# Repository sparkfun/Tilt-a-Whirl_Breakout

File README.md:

Tilt-a-Whirl Breakout Board
=====================

Note: The RPI-1031 IC is EOL and discontinuted by the manufacturer. Therefore, the tilt-a-whirl breakout has been retired.

[  
*RPI-1031 Tilt-a-Whirl Breakout(SEN-12011)*](https://www.sparkfun.com/products/12011)

The RPI-1031 tilt sensor is capable of sensing a change in orientation in four different directions: forward, back, left, or right.

Repository Contents
-------------------
* **/Firmware** - Example Arduino sketch for interfacing with the breakout board. 
* **/Hardware** - All Eagle design files (.brd, .sch)
* **/Production** - Test bed files and production panel files

Product Versions
----------------
* [SEN-12011 (RETIRED)](https://www.sparkfun.com/products/12011)- V12 of the Tilt-a-Whirl
* [SEN-10621 (RETIRED)](https://www.sparkfun.com/products/10621)- V11 of the Tilt-a-Whirl

License Information
-------------------
The hardware is released under [Creative Commons Share-alike 3.0](http://creativecommons.org/licenses/by-sa/3.0/).  
All other code is open source so please feel free to do anything you want with it; 
you buy me a beer if you use this and we meet someday ([Beerware license](http://en.wikipedia.org/wiki/Beerware)).

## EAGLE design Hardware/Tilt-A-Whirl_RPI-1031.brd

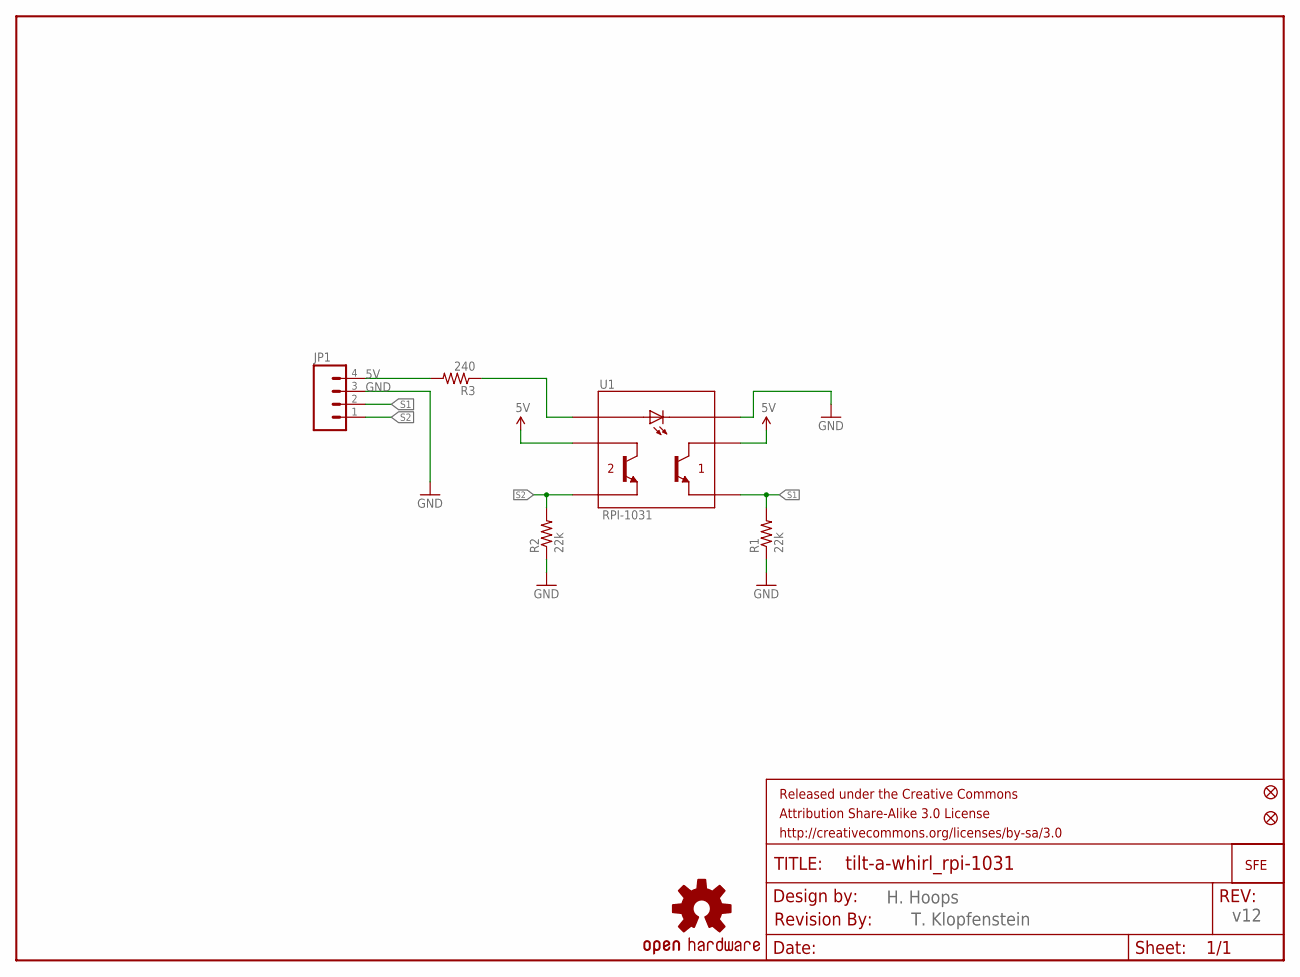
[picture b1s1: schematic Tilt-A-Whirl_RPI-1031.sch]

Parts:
FRAME1: FRAME-LETTER; CREATIVE_COMMONS
JP1: M04PTH; 1X04
JP2, JP3: FIDUCIAL1X2.5; FIDUCIAL-1X2.5
JP4: LOGO-SFESK; SFE-LOGO-FLAME
R1, R2: 22k; 0603-RES
R3: 240; 0603-RES
U1: RPI-1031
U$1: OSHW-LOGOS; OSHW-LOGO-S
U$2: REVISION

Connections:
5V: JP1.4, R3.2, U1.2 (C1), U1.5 (C2)
AN: R3.1, U1.6 (ANODE)
GND: JP1.3, R1.1, R2.1, U1.3 (CATHODE)
S1: JP1.2, R1.2, U1.1 (E1)
S2: JP1.1, R2.2, U1.4 (E2)

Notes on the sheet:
H. Hoops
T. Klopfenstein
v12

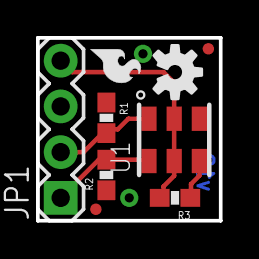
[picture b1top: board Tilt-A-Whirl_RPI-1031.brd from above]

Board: 2 copper layers, 10.2 x 10.2 mm, 11 parts (0 on the bottom side), 5 nets.

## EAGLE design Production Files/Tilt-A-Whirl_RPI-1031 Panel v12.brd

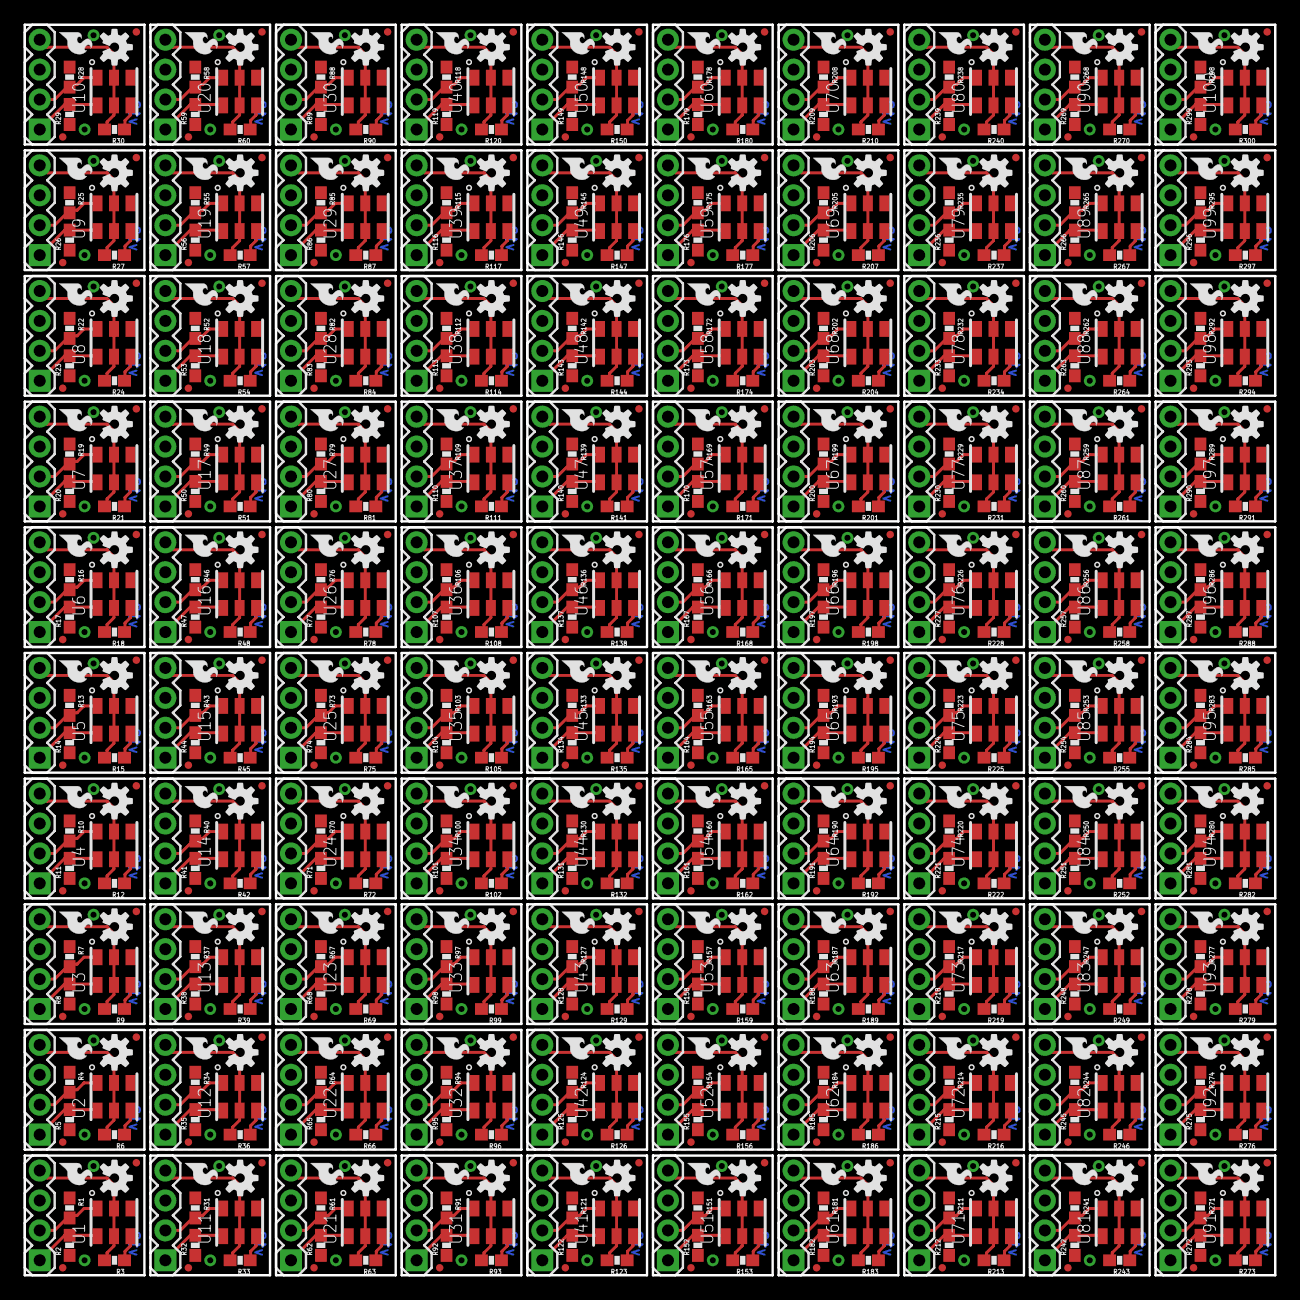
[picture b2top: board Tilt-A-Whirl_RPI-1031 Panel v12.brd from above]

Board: 2 copper layers, 106.2 x 106.2 mm, 900 parts (0 on the bottom side), 500 nets.

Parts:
JP1, JP6, JP10, JP14, JP18, JP22, JP26, JP30, JP34, JP38, JP42, JP46, JP50, JP54, JP58, JP62, JP66, JP70, JP74, JP78, JP82, JP86, JP90, JP94, JP98, JP102, JP106, JP110, JP114, JP118, JP122, JP126, JP130, JP134, JP138, JP142, JP146, JP150, JP154, JP158, JP162, JP166, JP170, JP174, JP178, JP182, JP186, JP190, JP194, JP198, JP202, JP206, JP210, JP214, JP218, JP222, JP226, JP230, JP234, JP238, JP242, JP246, JP250, JP254, JP258, JP262, JP266, JP270, JP274, JP278, JP282, JP286, JP290, JP294, JP298, JP302, JP306, JP310, JP314, JP318, JP322, JP326, JP330, JP334, JP338, JP342, JP346, JP350, JP354, JP358, JP362, JP366, JP370, JP374, JP378, JP382, JP386, JP390, JP394, JP398: 1X04
JP2, JP3, JP7, JP8, JP11, JP12, JP15, JP16, JP19, JP20, JP23, JP24, JP27, JP28, JP31, JP32, JP35, JP36, JP39, JP40, JP43, JP44, JP47, JP48, JP51, JP52, JP55, JP56, JP59, JP60, JP63, JP64, JP67, JP68, JP71, JP72, JP75, JP76, JP79, JP80, JP83, JP84, JP87, JP88, JP91, JP92, JP95, JP96, JP99, JP100, JP103, JP104, JP107, JP108, JP111, JP112, JP115, JP116, JP119, JP120, JP123, JP124, JP127, JP128, JP131, JP132, JP135, JP136, JP139, JP140, JP143, JP144, JP147, JP148, JP151, JP152, JP155, JP156, JP159, JP160, JP163, JP164, JP167, JP168, JP171, JP172, JP175, JP176, JP179, JP180, JP183, JP184, JP187, JP188, JP191, JP192, JP195, JP196, JP199, JP200, JP203, JP204, JP207, JP208, JP211, JP212, JP215, JP216, JP219, JP220, JP223, JP224, JP227, JP228, JP231, JP232, JP235, JP236, JP239, JP240, JP243, JP244, JP247, JP248, JP251, JP252, JP255, JP256, JP259, JP260, JP263, JP264, JP267, JP268, JP271, JP272, JP275, JP276, JP279, JP280, JP283, JP284, JP287, JP288, JP291, JP292, JP295, JP296, JP299, JP300, JP303, JP304, JP307, JP308, JP311, JP312, JP315, JP316, JP319, JP320, JP323, JP324, JP327, JP328, JP331, JP332, JP335, JP336, JP339, JP340, JP343, JP344, JP347, JP348, JP351, JP352, JP355, JP356, JP359, JP360, JP363, JP364, JP367, JP368, JP371, JP372, JP375, JP376, JP379, JP380, JP383, JP384, JP387, JP388, JP391, JP392, JP395, JP396, JP399, JP400: FIDUCIAL1X2.5; FIDUCIAL-1X2.5
JP4, JP5, JP9, JP13, JP17, JP21, JP25, JP29, JP33, JP37, JP41, JP45, JP49, JP53, JP57, JP61, JP65, JP69, JP73, JP77, JP81, JP85, JP89, JP93, JP97, JP101, JP105, JP109, JP113, JP117, JP121, JP125, JP129, JP133, JP137, JP141, JP145, JP149, JP153, JP157, JP161, JP165, JP169, JP173, JP177, JP181, JP185, JP189, JP193, JP197, JP201, JP205, JP209, JP213, JP217, JP221, JP225, JP229, JP233, JP237, JP241, JP245, JP249, JP253, JP257, JP261, JP265, JP269, JP273, JP277, JP281, JP285, JP289, JP293, JP297, JP301, JP305, JP309, JP313, JP317, JP321, JP325, JP329, JP333, JP337, JP341, JP345, JP349, JP353, JP357, JP361, JP365, JP369, JP373, JP377, JP381, JP385, JP389, JP393, JP397: LOGO-SFESK; SFE-LOGO-FLAME
R1, R2, R4, R5, R7, R8, R10, R11, R13, R14, R16, R17, R19, R20, R22, R23, R25, R26, R28, R29, R31, R32, R34, R35, R37, R38, R40, R41, R43, R44, R46, R47, R49, R50, R52, R53, R55, R56, R58, R59, R61, R62, R64, R65, R67, R68, R70, R71, R73, R74, R76, R77, R79, R80, R82, R83, R85, R86, R88, R89, R91, R92, R94, R95, R97, R98, R100, R101, R103, R104, R106, R107, R109, R110, R112, R113, R115, R116, R118, R119, R121, R122, R124, R125, R127, R128, R130, R131, R133, R134, R136, R137, R139, R140, R142, R143, R145, R146, R148, R149, R151, R152, R154, R155, R157, R158, R160, R161, R163, R164, R166, R167, R169, R170, R172, R173, R175, R176, R178, R179, R181, R182, R184, R185, R187, R188, R190, R191, R193, R194, R196, R197, R199, R200, R202, R203, R205, R206, R208, R209, R211, R212, R214, R215, R217, R218, R220, R221, R223, R224, R226, R227, R229, R230, R232, R233, R235, R236, R238, R239, R241, R242, R244, R245, R247, R248, R250, R251, R253, R254, R256, R257, R259, R260, R262, R263, R265, R266, R268, R269, R271, R272, R274, R275, R277, R278, R280, R281, R283, R284, R286, R287, R289, R290, R292, R293, R295, R296, R298, R299: 22k; 0603-RES
R3, R6, R9, R12, R15, R18, R21, R24, R27, R30, R33, R36, R39, R42, R45, R48, R51, R54, R57, R60, R63, R66, R69, R72, R75, R78, R81, R84, R87, R90, R93, R96, R99, R102, R105, R108, R111, R114, R117, R120, R123, R126, R129, R132, R135, R138, R141, R144, R147, R150, R153, R156, R159, R162, R165, R168, R171, R174, R177, R180, R183, R186, R189, R192, R195, R198, R201, R204, R207, R210, R213, R216, R219, R222, R225, R228, R231, R234, R237, R240, R243, R246, R249, R252, R255, R258, R261, R264, R267, R270, R273, R276, R279, R282, R285, R288, R291, R294, R297, R300: 240; 0603-RES
U1, U2, U3, U4, U5, U6, U7, U8, U9, U10, U11, U12, U13, U14, U15, U16, U17, U18, U19, U20, U21, U22, U23, U24, U25, U26, U27, U28, U29, U30, U31, U32, U33, U34, U35, U36, U37, U38, U39, U40, U41, U42, U43, U44, U45, U46, U47, U48, U49, U50, U51, U52, U53, U54, U55, U56, U57, U58, U59, U60, U61, U62, U63, U64, U65, U66, U67, U68, U69, U70, U71, U72, U73, U74, U75, U76, U77, U78, U79, U80, U81, U82, U83, U84, U85, U86, U87, U88, U89, U90, U91, U92, U93, U94, U95, U96, U97, U98, U99, U100: RPI-1031
U$1, U$2, U$3, U$4, U$5, U$6, U$7, U$8, U$9, U$10, U$11, U$12, U$13, U$14, U$15, U$16, U$17, U$18, U$19, U$20, U$21, U$22, U$23, U$24, U$25, U$26, U$27, U$28, U$29, U$30, U$31, U$32, U$33, U$34, U$35, U$36, U$37, U$38, U$39, U$40, U$41, U$42, U$43, U$44, U$45, U$46, U$47, U$48, U$49, U$50, U$51, U$52, U$53, U$54, U$55, U$56, U$57, U$58, U$59, U$60, U$61, U$62, U$63, U$64, U$65, U$66, U$67, U$68, U$69, U$70, U$71, U$72, U$73, U$74, U$75, U$76, U$77, U$78, U$79, U$80, U$81, U$82, U$83, U$84, U$85, U$86, U$87, U$88, U$89, U$90, U$91, U$92, U$93, U$94, U$95, U$96, U$97, U$98, U$99, U$100: OSHW-LOGOS; OSHW-LOGO-S

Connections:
5V: JP1.4, R3.2, U1.2, U1.5
5V1: JP6.4, R6.2, U2.2, U2.5
5V2: JP10.4, R9.2, U3.2, U3.5
5V3: JP14.4, R12.2, U4.2, U4.5
5V4: JP18.4, R15.2, U5.2, U5.5
5V5: JP22.4, R18.2, U6.2, U6.5
5V6: JP26.4, R21.2, U7.2, U7.5
5V7: JP30.4, R24.2, U8.2, U8.5
5V8: JP34.4, R27.2, U9.2, U9.5
5V9: JP38.4, R30.2, U10.2, U10.5
5V10: JP42.4, R33.2, U11.2, U11.5
5V11: JP46.4, R36.2, U12.2, U12.5
5V12: JP50.4, R39.2, U13.2, U13.5
5V13: JP54.4, R42.2, U14.2, U14.5
5V14: JP58.4, R45.2, U15.2, U15.5
5V15: JP62.4, R48.2, U16.2, U16.5
5V16: JP66.4, R51.2, U17.2, U17.5
5V17: JP70.4, R54.2, U18.2, U18.5
5V18: JP74.4, R57.2, U19.2, U19.5
5V19: JP78.4, R60.2, U20.2, U20.5
5V20: JP82.4, R63.2, U21.2, U21.5
5V21: JP86.4, R66.2, U22.2, U22.5
5V22: JP90.4, R69.2, U23.2, U23.5
5V23: JP94.4, R72.2, U24.2, U24.5
5V24: JP98.4, R75.2, U25.2, U25.5
5V25: JP102.4, R78.2, U26.2, U26.5
5V26: JP106.4, R81.2, U27.2, U27.5
5V27: JP110.4, R84.2, U28.2, U28.5
5V28: JP114.4, R87.2, U29.2, U29.5
5V29: JP118.4, R90.2, U30.2, U30.5
5V30: JP122.4, R93.2, U31.2, U31.5
5V31: JP126.4, R96.2, U32.2, U32.5
5V32: JP130.4, R99.2, U33.2, U33.5
5V33: JP134.4, R102.2, U34.2, U34.5
5V34: JP138.4, R105.2, U35.2, U35.5
5V35: JP142.4, R108.2, U36.2, U36.5
5V36: JP146.4, R111.2, U37.2, U37.5
5V37: JP150.4, R114.2, U38.2, U38.5
5V38: JP154.4, R117.2, U39.2, U39.5
5V39: JP158.4, R120.2, U40.2, U40.5
5V40: JP162.4, R123.2, U41.2, U41.5
5V41: JP166.4, R126.2, U42.2, U42.5
5V42: JP170.4, R129.2, U43.2, U43.5
5V43: JP174.4, R132.2, U44.2, U44.5
5V44: JP178.4, R135.2, U45.2, U45.5
5V45: JP182.4, R138.2, U46.2, U46.5
5V46: JP186.4, R141.2, U47.2, U47.5
5V47: JP190.4, R144.2, U48.2, U48.5
5V48: JP194.4, R147.2, U49.2, U49.5
5V49: JP198.4, R150.2, U50.2, U50.5
5V50: JP202.4, R153.2, U51.2, U51.5
5V51: JP206.4, R156.2, U52.2, U52.5
5V52: JP210.4, R159.2, U53.2, U53.5
5V53: JP214.4, R162.2, U54.2, U54.5
5V54: JP218.4, R165.2, U55.2, U55.5
5V55: JP222.4, R168.2, U56.2, U56.5
5V56: JP226.4, R171.2, U57.2, U57.5
5V57: JP230.4, R174.2, U58.2, U58.5
5V58: JP234.4, R177.2, U59.2, U59.5
5V59: JP238.4, R180.2, U60.2, U60.5
5V60: JP242.4, R183.2, U61.2, U61.5
5V61: JP246.4, R186.2, U62.2, U62.5
5V62: JP250.4, R189.2, U63.2, U63.5
5V63: JP254.4, R192.2, U64.2, U64.5
5V64: JP258.4, R195.2, U65.2, U65.5
5V65: JP262.4, R198.2, U66.2, U66.5
5V66: JP266.4, R201.2, U67.2, U67.5
5V67: JP270.4, R204.2, U68.2, U68.5
5V68: JP274.4, R207.2, U69.2, U69.5
5V69: JP278.4, R210.2, U70.2, U70.5
5V70: JP282.4, R213.2, U71.2, U71.5
5V71: JP286.4, R216.2, U72.2, U72.5
5V72: JP290.4, R219.2, U73.2, U73.5
5V73: JP294.4, R222.2, U74.2, U74.5
5V74: JP298.4, R225.2, U75.2, U75.5
5V75: JP302.4, R228.2, U76.2, U76.5
5V76: JP306.4, R231.2, U77.2, U77.5
5V77: JP310.4, R234.2, U78.2, U78.5
5V78: JP314.4, R237.2, U79.2, U79.5
5V79: JP318.4, R240.2, U80.2, U80.5
5V80: JP322.4, R243.2, U81.2, U81.5
5V81: JP326.4, R246.2, U82.2, U82.5
5V82: JP330.4, R249.2, U83.2, U83.5
5V83: JP334.4, R252.2, U84.2, U84.5
5V84: JP338.4, R255.2, U85.2, U85.5
5V85: JP342.4, R258.2, U86.2, U86.5
5V86: JP346.4, R261.2, U87.2, U87.5
5V87: JP350.4, R264.2, U88.2, U88.5
5V88: JP354.4, R267.2, U89.2, U89.5
5V89: JP358.4, R270.2, U90.2, U90.5
5V90: JP362.4, R273.2, U91.2, U91.5
5V91: JP366.4, R276.2, U92.2, U92.5
5V92: JP370.4, R279.2, U93.2, U93.5
5V93: JP374.4, R282.2, U94.2, U94.5
5V94: JP378.4, R285.2, U95.2, U95.5
5V95: JP382.4, R288.2, U96.2, U96.5
5V96: JP386.4, R291.2, U97.2, U97.5
5V97: JP390.4, R294.2, U98.2, U98.5
5V98: JP394.4, R297.2, U99.2, U99.5
5V99: JP398.4, R300.2, U100.2, U100.5
AN: R3.1, U1.6
AN1: R6.1, U2.6
AN2: R9.1, U3.6
AN3: R12.1, U4.6
AN4: R15.1, U5.6
AN5: R18.1, U6.6
AN6: R21.1, U7.6
AN7: R24.1, U8.6
AN8: R27.1, U9.6
AN9: R30.1, U10.6
AN10: R33.1, U11.6
AN11: R36.1, U12.6
AN12: R39.1, U13.6
AN13: R42.1, U14.6
AN14: R45.1, U15.6
AN15: R48.1, U16.6
AN16: R51.1, U17.6
AN17: R54.1, U18.6
AN18: R57.1, U19.6
AN19: R60.1, U20.6
AN20: R63.1, U21.6
AN21: R66.1, U22.6
AN22: R69.1, U23.6
AN23: R72.1, U24.6
AN24: R75.1, U25.6
AN25: R78.1, U26.6
AN26: R81.1, U27.6
AN27: R84.1, U28.6
AN28: R87.1, U29.6
AN29: R90.1, U30.6
AN30: R93.1, U31.6
AN31: R96.1, U32.6
AN32: R99.1, U33.6
AN33: R102.1, U34.6
AN34: R105.1, U35.6
AN35: R108.1, U36.6
AN36: R111.1, U37.6
AN37: R114.1, U38.6
AN38: R117.1, U39.6
AN39: R120.1, U40.6
AN40: R123.1, U41.6
AN41: R126.1, U42.6
AN42: R129.1, U43.6
AN43: R132.1, U44.6
AN44: R135.1, U45.6
AN45: R138.1, U46.6
AN46: R141.1, U47.6
AN47: R144.1, U48.6
AN48: R147.1, U49.6
AN49: R150.1, U50.6
AN50: R153.1, U51.6
AN51: R156.1, U52.6
AN52: R159.1, U53.6
AN53: R162.1, U54.6
AN54: R165.1, U55.6
AN55: R168.1, U56.6
AN56: R171.1, U57.6
AN57: R174.1, U58.6
AN58: R177.1, U59.6
AN59: R180.1, U60.6
AN60: R183.1, U61.6
AN61: R186.1, U62.6
AN62: R189.1, U63.6
AN63: R192.1, U64.6
AN64: R195.1, U65.6
AN65: R198.1, U66.6
AN66: R201.1, U67.6
AN67: R204.1, U68.6
AN68: R207.1, U69.6
AN69: R210.1, U70.6
AN70: R213.1, U71.6
AN71: R216.1, U72.6
AN72: R219.1, U73.6
AN73: R222.1, U74.6
AN74: R225.1, U75.6
AN75: R228.1, U76.6
AN76: R231.1, U77.6
AN77: R234.1, U78.6
AN78: R237.1, U79.6
AN79: R240.1, U80.6
AN80: R243.1, U81.6
AN81: R246.1, U82.6
AN82: R249.1, U83.6
AN83: R252.1, U84.6
AN84: R255.1, U85.6
AN85: R258.1, U86.6
AN86: R261.1, U87.6
AN87: R264.1, U88.6
AN88: R267.1, U89.6
AN89: R270.1, U90.6
AN90: R273.1, U91.6
AN91: R276.1, U92.6
AN92: R279.1, U93.6
AN93: R282.1, U94.6
AN94: R285.1, U95.6
AN95: R288.1, U96.6
AN96: R291.1, U97.6
AN97: R294.1, U98.6
AN98: R297.1, U99.6
AN99: R300.1, U100.6
GND: JP1.3, R1.1, R2.1, U1.3
GND1: JP6.3, R4.1, R5.1, U2.3
GND2: JP10.3, R7.1, R8.1, U3.3
GND3: JP14.3, R10.1, R11.1, U4.3
GND4: JP18.3, R13.1, R14.1, U5.3
GND5: JP22.3, R16.1, R17.1, U6.3
GND6: JP26.3, R19.1, R20.1, U7.3
GND7: JP30.3, R22.1, R23.1, U8.3
GND8: JP34.3, R25.1, R26.1, U9.3
GND9: JP38.3, R28.1, R29.1, U10.3
GND10: JP42.3, R31.1, R32.1, U11.3
GND11: JP46.3, R34.1, R35.1, U12.3
GND12: JP50.3, R37.1, R38.1, U13.3
GND13: JP54.3, R40.1, R41.1, U14.3
GND14: JP58.3, R43.1, R44.1, U15.3
GND15: JP62.3, R46.1, R47.1, U16.3
GND16: JP66.3, R49.1, R50.1, U17.3
GND17: JP70.3, R52.1, R53.1, U18.3
GND18: JP74.3, R55.1, R56.1, U19.3
GND19: JP78.3, R58.1, R59.1, U20.3
GND20: JP82.3, R61.1, R62.1, U21.3
GND21: JP86.3, R64.1, R65.1, U22.3
GND22: JP90.3, R67.1, R68.1, U23.3
GND23: JP94.3, R70.1, R71.1, U24.3
GND24: JP98.3, R73.1, R74.1, U25.3
GND25: JP102.3, R76.1, R77.1, U26.3
GND26: JP106.3, R79.1, R80.1, U27.3
GND27: JP110.3, R82.1, R83.1, U28.3
GND28: JP114.3, R85.1, R86.1, U29.3
GND29: JP118.3, R88.1, R89.1, U30.3
GND30: JP122.3, R91.1, R92.1, U31.3
GND31: JP126.3, R94.1, R95.1, U32.3
GND32: JP130.3, R97.1, R98.1, U33.3
GND33: JP134.3, R100.1, R101.1, U34.3
GND34: JP138.3, R103.1, R104.1, U35.3
GND35: JP142.3, R106.1, R107.1, U36.3
GND36: JP146.3, R109.1, R110.1, U37.3
GND37: JP150.3, R112.1, R113.1, U38.3
GND38: JP154.3, R115.1, R116.1, U39.3
GND39: JP158.3, R118.1, R119.1, U40.3
GND40: JP162.3, R121.1, R122.1, U41.3
GND41: JP166.3, R124.1, R125.1, U42.3
GND42: JP170.3, R127.1, R128.1, U43.3
GND43: JP174.3, R130.1, R131.1, U44.3
GND44: JP178.3, R133.1, R134.1, U45.3
GND45: JP182.3, R136.1, R137.1, U46.3
GND46: JP186.3, R139.1, R140.1, U47.3
GND47: JP190.3, R142.1, R143.1, U48.3
GND48: JP194.3, R145.1, R146.1, U49.3
GND49: JP198.3, R148.1, R149.1, U50.3
GND50: JP202.3, R151.1, R152.1, U51.3
GND51: JP206.3, R154.1, R155.1, U52.3
GND52: JP210.3, R157.1, R158.1, U53.3
GND53: JP214.3, R160.1, R161.1, U54.3
GND54: JP218.3, R163.1, R164.1, U55.3
GND55: JP222.3, R166.1, R167.1, U56.3
GND56: JP226.3, R169.1, R170.1, U57.3
GND57: JP230.3, R172.1, R173.1, U58.3
GND58: JP234.3, R175.1, R176.1, U59.3
GND59: JP238.3, R178.1, R179.1, U60.3
GND60: JP242.3, R181.1, R182.1, U61.3
GND61: JP246.3, R184.1, R185.1, U62.3
GND62: JP250.3, R187.1, R188.1, U63.3
GND63: JP254.3, R190.1, R191.1, U64.3
GND64: JP258.3, R193.1, R194.1, U65.3
GND65: JP262.3, R196.1, R197.1, U66.3
GND66: JP266.3, R199.1, R200.1, U67.3
GND67: JP270.3, R202.1, R203.1, U68.3
GND68: JP274.3, R205.1, R206.1, U69.3
GND69: JP278.3, R208.1, R209.1, U70.3
GND70: JP282.3, R211.1, R212.1, U71.3
GND71: JP286.3, R214.1, R215.1, U72.3
GND72: JP290.3, R217.1, R218.1, U73.3
GND73: JP294.3, R220.1, R221.1, U74.3
GND74: JP298.3, R223.1, R224.1, U75.3
GND75: JP302.3, R226.1, R227.1, U76.3
GND76: JP306.3, R229.1, R230.1, U77.3
GND77: JP310.3, R232.1, R233.1, U78.3
GND78: JP314.3, R235.1, R236.1, U79.3
GND79: JP318.3, R238.1, R239.1, U80.3
GND80: JP322.3, R241.1, R242.1, U81.3
GND81: JP326.3, R244.1, R245.1, U82.3
GND82: JP330.3, R247.1, R248.1, U83.3
GND83: JP334.3, R250.1, R251.1, U84.3
GND84: JP338.3, R253.1, R254.1, U85.3
GND85: JP342.3, R256.1, R257.1, U86.3
GND86: JP346.3, R259.1, R260.1, U87.3
GND87: JP350.3, R262.1, R263.1, U88.3
GND88: JP354.3, R265.1, R266.1, U89.3
GND89: JP358.3, R268.1, R269.1, U90.3
GND90: JP362.3, R271.1, R272.1, U91.3
GND91: JP366.3, R274.1, R275.1, U92.3
GND92: JP370.3, R277.1, R278.1, U93.3
GND93: JP374.3, R280.1, R281.1, U94.3
GND94: JP378.3, R283.1, R284.1, U95.3
GND95: JP382.3, R286.1, R287.1, U96.3
GND96: JP386.3, R289.1, R290.1, U97.3
GND97: JP390.3, R292.1, R293.1, U98.3
GND98: JP394.3, R295.1, R296.1, U99.3
GND99: JP398.3, R298.1, R299.1, U100.3
S1: JP1.2, R1.2, U1.1
S2: JP1.1, R2.2, U1.4
S3: JP6.2, R4.2, U2.1
S4: JP6.1, R5.2, U2.4
S5: JP10.2, R7.2, U3.1
S6: JP10.1, R8.2, U3.4
S7: JP14.2, R10.2, U4.1
S8: JP14.1, R11.2, U4.4
S9: JP18.2, R13.2, U5.1
S10: JP18.1, R14.2, U5.4
S11: JP22.2, R16.2, U6.1
S12: JP22.1, R17.2, U6.4
S13: JP26.2, R19.2, U7.1
S14: JP26.1, R20.2, U7.4
S15: JP30.2, R22.2, U8.1
S16: JP30.1, R23.2, U8.4
S17: JP34.2, R25.2, U9.1
S18: JP34.1, R26.2, U9.4
S19: JP38.2, R28.2, U10.1
S20: JP38.1, R29.2, U10.4
S21: JP42.2, R31.2, U11.1
S22: JP42.1, R32.2, U11.4
S23: JP46.2, R34.2, U12.1
S24: JP46.1, R35.2, U12.4
S25: JP50.2, R37.2, U13.1
S26: JP50.1, R38.2, U13.4
S27: JP54.2, R40.2, U14.1
S28: JP54.1, R41.2, U14.4
S29: JP58.2, R43.2, U15.1
S30: JP58.1, R44.2, U15.4
S31: JP62.2, R46.2, U16.1
S32: JP62.1, R47.2, U16.4
S33: JP66.2, R49.2, U17.1
S34: JP66.1, R50.2, U17.4
S35: JP70.2, R52.2, U18.1
S36: JP70.1, R53.2, U18.4
S37: JP74.2, R55.2, U19.1
S38: JP74.1, R56.2, U19.4
S39: JP78.2, R58.2, U20.1
S40: JP78.1, R59.2, U20.4
S41: JP82.2, R61.2, U21.1
S42: JP82.1, R62.2, U21.4
S43: JP86.2, R64.2, U22.1
S44: JP86.1, R65.2, U22.4
S45: JP90.2, R67.2, U23.1
S46: JP90.1, R68.2, U23.4
S47: JP94.2, R70.2, U24.1
S48: JP94.1, R71.2, U24.4
S49: JP98.2, R73.2, U25.1
S50: JP98.1, R74.2, U25.4
S51: JP102.2, R76.2, U26.1
S52: JP102.1, R77.2, U26.4
S53: JP106.2, R79.2, U27.1
S54: JP106.1, R80.2, U27.4
S55: JP110.2, R82.2, U28.1
S56: JP110.1, R83.2, U28.4
S57: JP114.2, R85.2, U29.1
S58: JP114.1, R86.2, U29.4
S59: JP118.2, R88.2, U30.1
S60: JP118.1, R89.2, U30.4
S61: JP122.2, R91.2, U31.1
S62: JP122.1, R92.2, U31.4
S63: JP126.2, R94.2, U32.1
S64: JP126.1, R95.2, U32.4
S65: JP130.2, R97.2, U33.1
S66: JP130.1, R98.2, U33.4
S67: JP134.2, R100.2, U34.1
S68: JP134.1, R101.2, U34.4
S69: JP138.2, R103.2, U35.1
S70: JP138.1, R104.2, U35.4
S71: JP142.2, R106.2, U36.1
S72: JP142.1, R107.2, U36.4
S73: JP146.2, R109.2, U37.1
S74: JP146.1, R110.2, U37.4
S75: JP150.2, R112.2, U38.1
S76: JP150.1, R113.2, U38.4
S77: JP154.2, R115.2, U39.1
S78: JP154.1, R116.2, U39.4
S79: JP158.2, R118.2, U40.1
S80: JP158.1, R119.2, U40.4
S81: JP162.2, R121.2, U41.1
S82: JP162.1, R122.2, U41.4
S83: JP166.2, R124.2, U42.1
S84: JP166.1, R125.2, U42.4
S85: JP170.2, R127.2, U43.1
S86: JP170.1, R128.2, U43.4
S87: JP174.2, R130.2, U44.1
S88: JP174.1, R131.2, U44.4
S89: JP178.2, R133.2, U45.1
S90: JP178.1, R134.2, U45.4
S91: JP182.2, R136.2, U46.1
S92: JP182.1, R137.2, U46.4
S93: JP186.2, R139.2, U47.1
S94: JP186.1, R140.2, U47.4
S95: JP190.2, R142.2, U48.1
S96: JP190.1, R143.2, U48.4
S97: JP194.2, R145.2, U49.1
S98: JP194.1, R146.2, U49.4
S99: JP198.2, R148.2, U50.1
S100: JP198.1, R149.2, U50.4
S101: JP202.2, R151.2, U51.1
S102: JP202.1, R152.2, U51.4
S103: JP206.2, R154.2, U52.1
S104: JP206.1, R155.2, U52.4
S105: JP210.2, R157.2, U53.1
S106: JP210.1, R158.2, U53.4
S107: JP214.2, R160.2, U54.1
S108: JP214.1, R161.2, U54.4
S109: JP218.2, R163.2, U55.1
S110: JP218.1, R164.2, U55.4
S111: JP222.2, R166.2, U56.1
S112: JP222.1, R167.2, U56.4
S113: JP226.2, R169.2, U57.1
S114: JP226.1, R170.2, U57.4
S115: JP230.2, R172.2, U58.1
S116: JP230.1, R173.2, U58.4
S117: JP234.2, R175.2, U59.1
S118: JP234.1, R176.2, U59.4
S119: JP238.2, R178.2, U60.1
S120: JP238.1, R179.2, U60.4
S121: JP242.2, R181.2, U61.1
S122: JP242.1, R182.2, U61.4
S123: JP246.2, R184.2, U62.1
S124: JP246.1, R185.2, U62.4
S125: JP250.2, R187.2, U63.1
S126: JP250.1, R188.2, U63.4
S127: JP254.2, R190.2, U64.1
S128: JP254.1, R191.2, U64.4
S129: JP258.2, R193.2, U65.1
S130: JP258.1, R194.2, U65.4
S131: JP262.2, R196.2, U66.1
S132: JP262.1, R197.2, U66.4
S133: JP266.2, R199.2, U67.1
S134: JP266.1, R200.2, U67.4
S135: JP270.2, R202.2, U68.1
S136: JP270.1, R203.2, U68.4
S137: JP274.2, R205.2, U69.1
S138: JP274.1, R206.2, U69.4
S139: JP278.2, R208.2, U70.1
S140: JP278.1, R209.2, U70.4
S141: JP282.2, R211.2, U71.1
S142: JP282.1, R212.2, U71.4
S143: JP286.2, R214.2, U72.1
S144: JP286.1, R215.2, U72.4
S145: JP290.2, R217.2, U73.1
S146: JP290.1, R218.2, U73.4
S147: JP294.2, R220.2, U74.1
S148: JP294.1, R221.2, U74.4
S149: JP298.2, R223.2, U75.1
S150: JP298.1, R224.2, U75.4
S151: JP302.2, R226.2, U76.1
S152: JP302.1, R227.2, U76.4
S153: JP306.2, R229.2, U77.1
S154: JP306.1, R230.2, U77.4
S155: JP310.2, R232.2, U78.1
S156: JP310.1, R233.2, U78.4
S157: JP314.2, R235.2, U79.1
S158: JP314.1, R236.2, U79.4
S159: JP318.2, R238.2, U80.1
S160: JP318.1, R239.2, U80.4
S161: JP322.2, R241.2, U81.1
S162: JP322.1, R242.2, U81.4
S163: JP326.2, R244.2, U82.1
S164: JP326.1, R245.2, U82.4
S165: JP330.2, R247.2, U83.1
S166: JP330.1, R248.2, U83.4
S167: JP334.2, R250.2, U84.1
S168: JP334.1, R251.2, U84.4
S169: JP338.2, R253.2, U85.1
S170: JP338.1, R254.2, U85.4
S171: JP342.2, R256.2, U86.1
S172: JP342.1, R257.2, U86.4
S173: JP346.2, R259.2, U87.1
S174: JP346.1, R260.2, U87.4
S175: JP350.2, R262.2, U88.1
S176: JP350.1, R263.2, U88.4
S177: JP354.2, R265.2, U89.1
S178: JP354.1, R266.2, U89.4
S179: JP358.2, R268.2, U90.1
S180: JP358.1, R269.2, U90.4
S181: JP362.2, R271.2, U91.1
S182: JP362.1, R272.2, U91.4
S183: JP366.2, R274.2, U92.1
S184: JP366.1, R275.2, U92.4
S185: JP370.2, R277.2, U93.1
S186: JP370.1, R278.2, U93.4
S187: JP374.2, R280.2, U94.1
S188: JP374.1, R281.2, U94.4
S189: JP378.2, R283.2, U95.1
S190: JP378.1, R284.2, U95.4
S191: JP382.2, R286.2, U96.1
S192: JP382.1, R287.2, U96.4
S193: JP386.2, R289.2, U97.1
S194: JP386.1, R290.2, U97.4
S195: JP390.2, R292.2, U98.1
S196: JP390.1, R293.2, U98.4
S197: JP394.2, R295.2, U99.1
S198: JP394.1, R296.2, U99.4
S199: JP398.2, R298.2, U100.1
S200: JP398.1, R299.2, U100.4

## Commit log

2013-07-29 Update board files and README
2013-08-05 Updating board/schematic from review
2013-08-06 production ready v12
2013-09-30 Adding firmware and updating to v12

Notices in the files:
parts and their libraries:
SparkFun-Aesthetics: Licensing: CC v3.0 Share-Alike You are welcome to use this library for commercial purposes.
SparkFun-Aesthetics: Released under the Creative Commons Attribution Share-Alike 3.0 License
SparkFun-Aesthetics: Released under the Creative Commons
